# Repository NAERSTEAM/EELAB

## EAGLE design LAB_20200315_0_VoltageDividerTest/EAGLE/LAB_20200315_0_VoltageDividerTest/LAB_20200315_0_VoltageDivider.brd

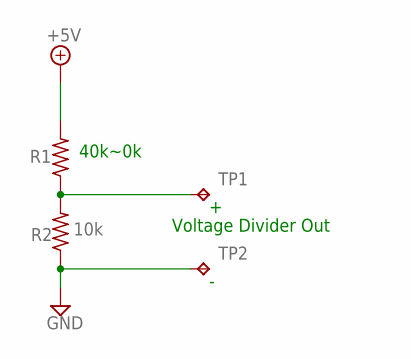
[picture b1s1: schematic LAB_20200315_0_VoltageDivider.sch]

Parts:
R1: R-US_0207/12; 0207/12
R2: 10k; 0207/12
TP1, TP2: TPB1,27; B1,27

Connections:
+5V: R1.2
GND: R2.1, TP2.TP
unnamed: R1.1, R2.2, TP1.TP

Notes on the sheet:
40k~0k
Voltage Divider Out

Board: 2 copper layers, 4 parts (0 on the bottom side), 2 nets, no tracks yet.

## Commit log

2020-02-26 added LAB_20200225_1 traffic light with button
2020-02-26 added LAB_20200225_0 traffic light
2020-02-26 added LAB_20200226_0 LED light
2020-02-26 added LAB_20200226_1 LED with switch
2020-03-02 added LAB_20200302_5 LED LED control by photoresistor
2020-03-03 added LAB_20200303 photosensitive monitor
2020-03-05 LAB_20200305_0 comport read
2020-03-05 Arduino UART receving framework for LAB_20200305_1
2020-03-05 Added PIN2 control for LAB_20200305_1
2020-03-05 LAB_20200305_1 COMPort test
2020-03-09 added LAB_20200309_0 LAB_20200309_1 servo test with/without VR
2020-03-16 added resource for LAB_20200315_0 Voltage Divider test,LAB_20200315_1 Flex sensor test wiht servo, Module_20200316_0 GloveControl
2020-04-01 added Module_VoltageDivider, added Project_Glovedcontrolrobot, project RPSRobot
2020-04-02 Added score,random gesture functions for RSPRobot, Updated documents for GlovedControl robot
2020-04-07 Added LED driver,Segdisplay driver, integration test for RSPRobot FW. Added EELAB Module_20200404_0
2020-04-07 Added EELAB Module_20200404_0
2020-04-08 Added ANN version for RPSRobot project. Fixed incorrect matchscore table in RPS FW
2020-04-08 Added machine learning PC App for the RSP project
2020-04-16 added buzzer and preparing gesture for Project RPSRobot
2020-05-17 Added scoreboard
2020-05-30 Added "LAB_20200530_0_hand sign recognition"
2020-06-03 Fixed issue #2 "the object box does not be displayed on the live window"
2020-06-04 added the example RSP game based on imageAI -LAB_20200530_0
2020-06-09 Added LAB_20200609_0_LightSensorWithNPN/LAB_20200609_0_LightSensorWithNPN
2020-06-15 Added LAB_20200530_0_HandSignRecognition/
2020-07-03 new file: LAB_20200225_0_TrafficLight/LAB_20200225_0/EAGLE/Module 20200225_0_Traffic Light.sch new file: LAB_20200225_0_TrafficLight/LAB_20200225_0/LAB_20200225_0.xlsx new file: LAB_20200622_0_Dispen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
2020-07-06 Added module 0622 dispenser
2020-07-24 several updates
2020-07-28 Update documents
2020-07-28 Updated documents
2020-08-01 Project_RSPImageRobot_20200801_0
2020-08-03 [Project RSPImageRobot]added audio notice for game flow
2020-08-03 [Project_RSPImageRobot_20200801_0]Added Chinese audio notice(win and lose) for gmae flow
2020-09-14 Serveral updates
2020-09-20 Added Lesson_20200914_0_ProjectRSPImageRobot_Review/Lesson_20200914_0_ProjectRSPImageRobot_Review Updated several documents
